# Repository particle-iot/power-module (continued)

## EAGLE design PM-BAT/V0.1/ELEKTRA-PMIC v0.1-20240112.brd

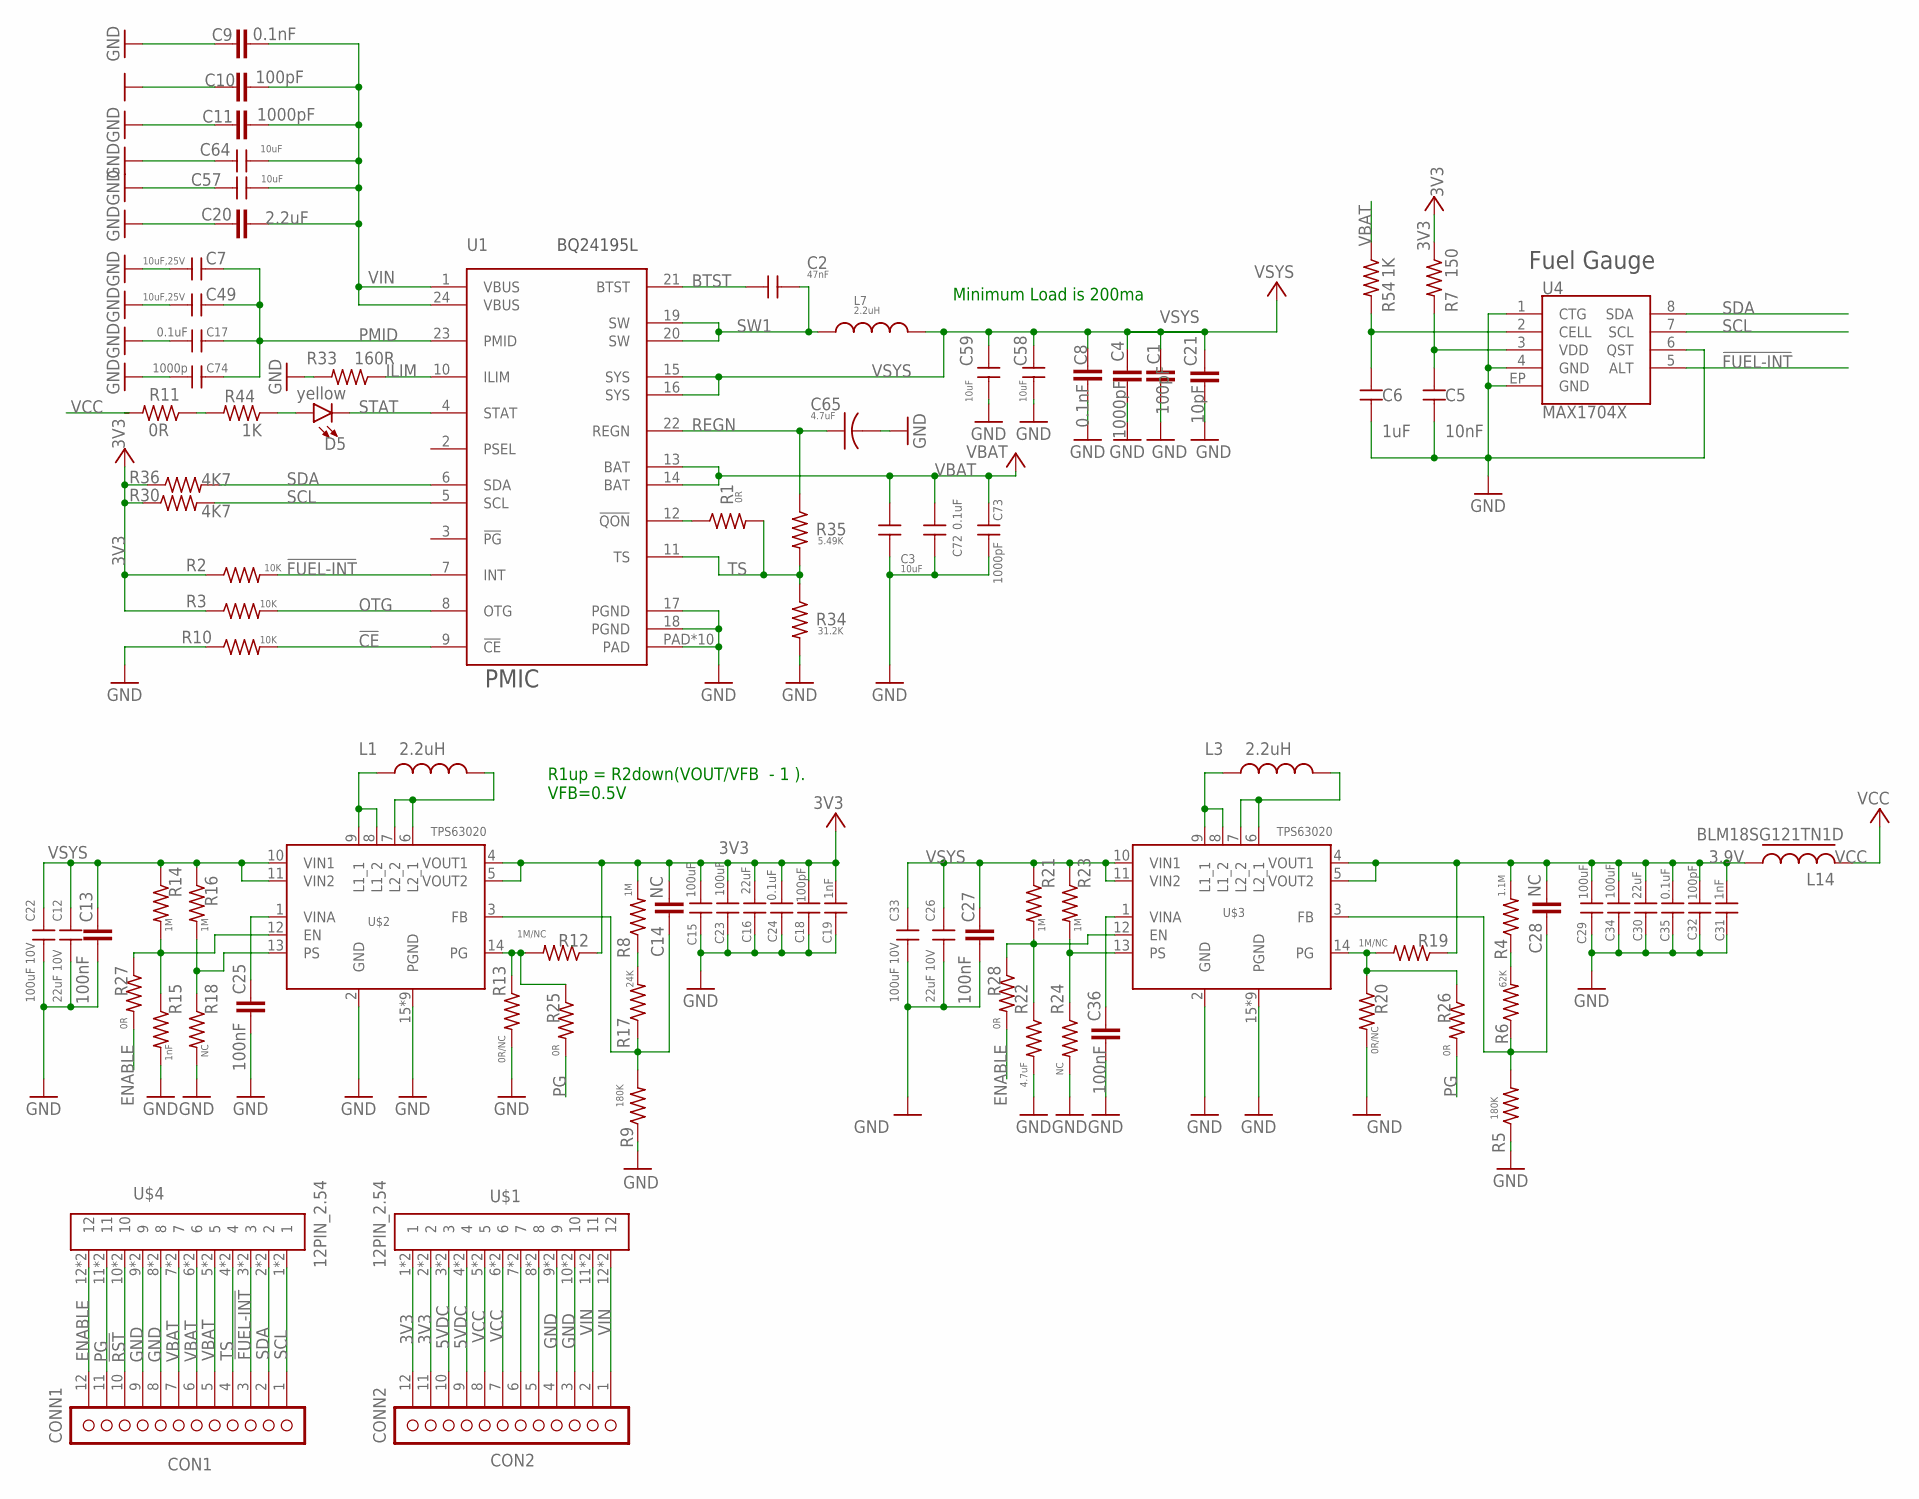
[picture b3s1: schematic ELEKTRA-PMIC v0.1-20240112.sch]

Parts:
C1, C10: 100pF; C0402_B
C2: 47nF; C-0402
C3: 10uF; C0603
C4, C11: 1000pF; C0402_B
C5: 10nF; C0402
C6: 1uF; C0402
C7, C49: 10uF,25V; C-0603A
C8, C9: 0.1nF; C0402_B
C12, C26: 22uF 10V; C0805
C13, C25, C27, C36: 100nF; C0402_B
C14, C28: NC; C0402_B
C15, C23, C29, C34: 100uF; C1206
C16, C30: 22uF; C-0603A
C17, C24, C35: 0.1uF; C0402
C18, C32: 100pF; C0402
C19, C31: 1nF; C0402
C20: 2.2uF; C0402_B
C21: 10pF; C0402_B
C22, C33: 100uF 10V; C1206
C57, C58, C59, C64: 10uF; C-0603A
C65: 4.7uF; C0603_B
C72: 0.1uF; C-0402
C73: 1000pF; C-0402
C74: 1000p; C-0402
CONN1: CON1; 1X12_SMD_STRAIGHT
CONN2: CON2; 1X12_SMD_STRAIGHT
D5: yellow; LED-0603
L1, L3: 2.2uH; INDUCTOR-VLS-E
L7: 2.2uH; INDUCTOR-4040
L14: BLM18SG121TN1D; R-0603A
R1, R11, R25, R26, R27, R28: 0R; R0402_B
R2, R3, R10: 10K; R0402_B
R4: 1.1M; R0402_B
R5, R9: 180K; R0402_B
R6: 62K; R0402_B
R7: 150; R0402_B
R8, R14, R16, R21, R23: 1M; R0402_B
R12, R19: 1M/NC; R0402_B
R13, R20: 0R/NC; R0402_B
R15: 1nF; R0402_B
R17: 24K; R0402_B
R18, R24: NC; R0402_B
R22: 4.7uF; R0402_B
R30, R36: 4K7; R0402_B
R33: 160R; R0402_B
R34: 31.2K; R0402_B
R35: 5.49K; R0402_B
R44, R54: 1K; R0402_B
U1: BQ24195L; QFN24
U4: MAX1704X; TDFN-8
U$1, U$4: 12PIN_2.54
U$2, U$3: TPS63020

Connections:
3.9V: C28.2, C29.1, C30.1, C31.1, C32.1, C34.1, C35.1, L14.2, R4.2, R19.1, U$3.4 (VOUT1), U$3.5 (VOUT2)
3V3: C14.2, C15.1, C16.1, C18.1, C19.1, C23.1, C24.1, CONN2.11, CONN2.12, R2.1, R3.1, R7.1, R8.2, R12.1, R30.1, R36.1, U$1.1, U$1.2, U$1.P$1 (1), U$1.P$2 (2), U$2.4 (VOUT1), U$2.5 (VOUT2)
5VDC: CONN2.9, CONN2.10, U$1.3, U$1.4, U$1.P$3 (3), U$1.P$4 (4)
!CE: R10.2, U1.9 (!CE)
!FUEL-INT: CONN1.3, R2.2, U1.7 (INT), U4.5 (ALT), U$4.3, U$4.P$3 (3)
!RST: CONN1.10, U$4.10, U$4.P$10 (10)
BTST: C2.1, U1.21 (BTST)
ENABLE: CONN1.12, R27.2, R28.2, U$4.12, U$4.P$12 (12)
GND: C1.1, C3.2, C4.1, C5.2, C6.2, C7.2, C8.1, C9.1, C10.1, C11.1, C12.2, C13.1, C15.2, C16.2, C17.1, C18.2, C19.2, C20.1, C21.1, C22.2, C23.2, C24.2, C25.1, C26.2, C27.1, C29.2, C30.2, C31.2, C32.2, C33.2, C34.2, C35.2, C36.1, C49.2, C57.2, C58.2, C59.2, C64.2, C65.2, C72.2, C73.2, C74.1, CONN1.8, CONN1.9, CONN2.3, CONN2.4, R5.1, R9.1, R10.1, R13.2, R15.2, R18.2, R20.2, R22.2, R24.2, R33.2, R34.2, U1.17 (PGND), U1.18 (PGND), U1.PAD, U1.PAD@1 (PAD), U1.PAD@2 (PAD), U1.PAD@3 (PAD), U1.PAD@4 (PAD), U1.PAD@5 (PAD), U1.PAD@6 (PAD), U1.PAD@7 (PAD), U1.PAD@8 (PAD), U1.PAD@9 (PAD), U4.1 (CTG), U4.4 (GND), U4.6 (QST), U4.EP (GND), U$1.9, U$1.10, U$1.P$9 (9), U$1.P$10 (10), U$2.2 (GND), U$2.15 (PGND), U$2.16 (PGND), U$2.17 (PGND), U$2.18 (PGND), U$2.19 (PGND), U$2.20 (PGND), U$2.21 (PGND), U$2.22 (PGND), U$2.23 (PGND), U$3.2 (GND), U$3.15 (PGND), U$3.16 (PGND), U$3.17 (PGND), U$3.18 (PGND), U$3.19 (PGND), U$3.20 (PGND), U$3.21 (PGND), U$3.22 (PGND), U$3.23 (PGND), U$4.8, U$4.9, U$4.P$8 (8), U$4.P$9 (9)
ILIM: R33.1, U1.10 (ILIM)
unnamed: R1.1, U1.12 (!QON)
unnamed: R11.1, R44.2
unnamed: D5.A, R44.1
unnamed: C14.1, R9.2, R17.1, U$2.3 (FB)
unnamed: C28.1, R5.2, R6.1, U$3.3 (FB)
unnamed: CONN2.6, U$1.7, U$1.P$7 (7)
unnamed: R8.1, R17.2
unnamed: R4.1, R6.2
unnamed: CONN2.5, U$1.8, U$1.P$8 (8)
unnamed: L3.P$1 (1), U$3.8 (L1_2), U$3.9 (L1_1)
unnamed: L1.P$1 (1), U$2.8 (L1_2), U$2.9 (L1_1)
unnamed: R12.2, R13.1, R25.1, U$2.14 (PG)
unnamed: R14.2, R15.1, R27.1, U$2.12 (EN)
unnamed: R16.2, R18.1, U$2.13 (PS)
unnamed: L3.P$2 (2), U$3.6 (L2_1), U$3.7 (L2_2)
unnamed: L1.P$2 (2), U$2.6 (L2_1), U$2.7 (L2_2)
unnamed: C25.2, U$2.1 (VINA)
unnamed: C36.2, U$3.1 (VINA)
unnamed: R19.2, R20.1, R26.1, U$3.14 (PG)
unnamed: R21.2, R22.1, R28.1, U$3.12 (EN)
unnamed: R23.2, R24.1, U$3.13 (PS)
unnamed: C5.1, R7.2, U4.3 (VDD)
unnamed: C6.1, R54.2, U4.2 (CELL)
OTG: R3.2, U1.8 (OTG)
PG: CONN1.11, R25.2, R26.2, U$4.11, U$4.P$11 (11)
PMID: C7.1, C17.2, C49.1, C74.2, U1.23 (PMID)
REGN: C65.1, R35.1, U1.22 (REGN)
SCL: CONN1.1, R30.2, U1.5 (SCL), U4.7 (SCL), U$4.1, U$4.P$1 (1)
SDA: CONN1.2, R36.2, U1.6 (SDA), U4.8 (SDA), U$4.2, U$4.P$2 (2)
STAT: D5.C, U1.4 (STAT)
SW1: C2.2, L7.P$1 (1), U1.19 (SW), U1.20 (SW)
TS: CONN1.4, R1.2, R34.1, R35.2, U1.11 (TS), U$4.4, U$4.P$4 (4)
VBAT: C3.1, C72.1, C73.1, CONN1.5, CONN1.6, CONN1.7, R54.1, U1.13 (BAT), U1.14 (BAT), U$4.5, U$4.6, U$4.7, U$4.P$5 (5), U$4.P$6 (6), U$4.P$7 (7)
VCC: CONN2.7, CONN2.8, L14.1, R11.2, U$1.5, U$1.6, U$1.P$5 (5), U$1.P$6 (6)
VIN: C9.2, C10.2, C11.2, C20.2, C57.1, C64.1, CONN2.1, CONN2.2, U1.1 (VBUS), U1.24 (VBUS), U$1.11, U$1.12, U$1.P$11 (11), U$1.P$12 (12)
VSYS: C1.2, C4.2, C8.2, C12.1, C13.2, C21.2, C22.1, C26.1, C27.2, C33.1, C58.1, C59.1, L7.P$2 (2), R14.1, R16.1, R21.1, R23.1, U1.15 (SYS), U1.16 (SYS), U$2.10 (VIN1), U$2.11 (VIN2), U$3.10 (VIN1), U$3.11 (VIN2)

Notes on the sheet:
Minimum Load is 200ma
PMIC
Fuel Gauge
R1up = R2down(VOUT/VFB - 1 ). VFB=0.5V

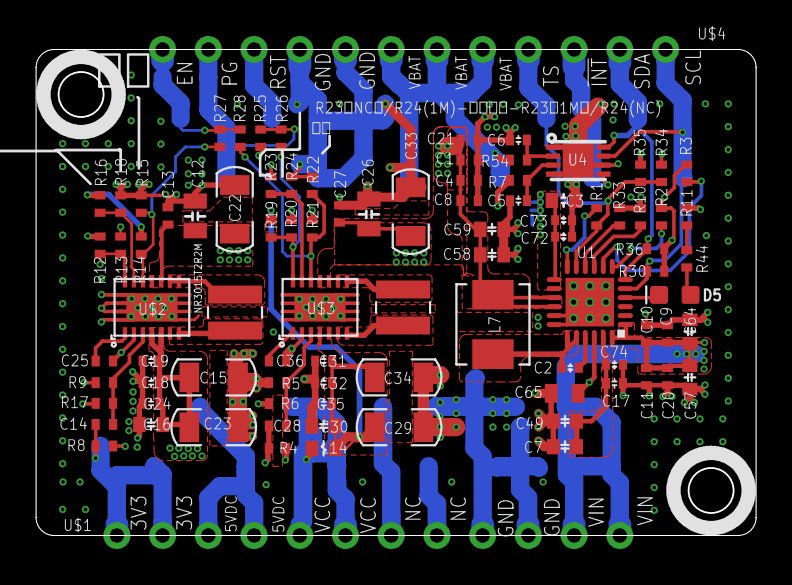
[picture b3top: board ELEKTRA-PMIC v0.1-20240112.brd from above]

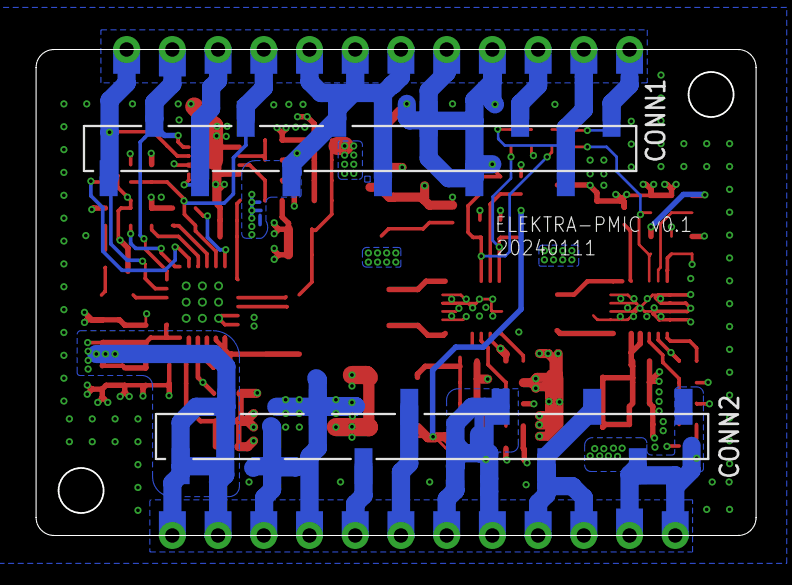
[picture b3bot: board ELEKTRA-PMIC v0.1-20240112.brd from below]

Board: 4 copper layers, 40.0 x 27.0 mm, 93 parts (2 on the bottom side), 46 nets.

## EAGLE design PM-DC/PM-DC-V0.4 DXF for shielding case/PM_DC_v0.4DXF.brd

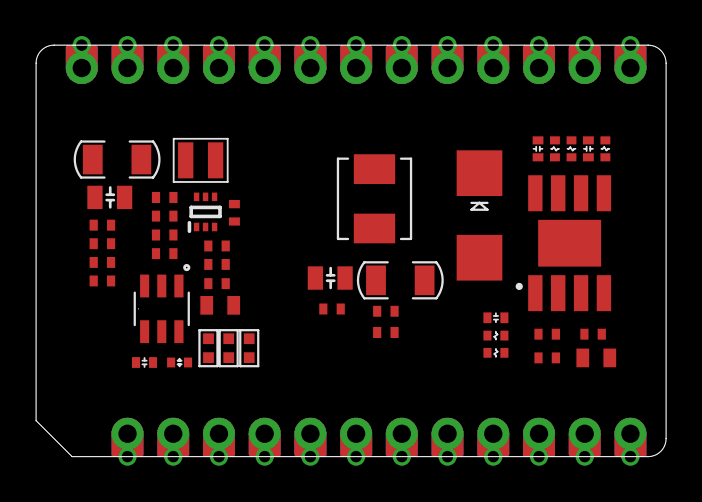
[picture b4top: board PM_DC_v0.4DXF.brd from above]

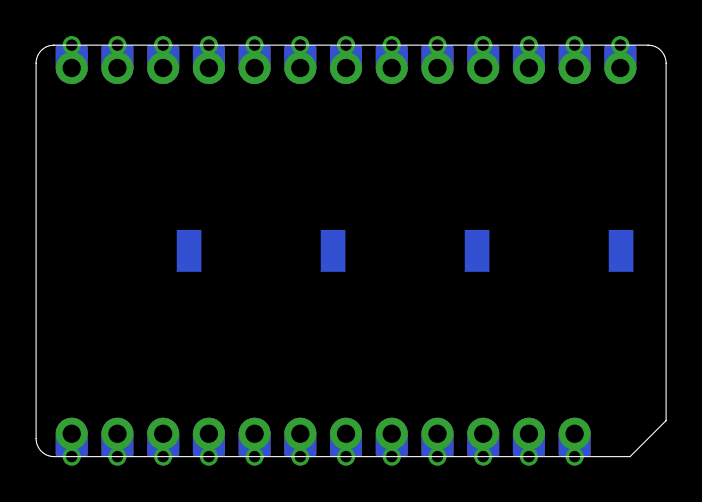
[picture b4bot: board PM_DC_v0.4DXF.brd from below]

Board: 2 copper layers, 35.0 x 22.9 mm, 49 parts (4 on the bottom side), 19 nets, no tracks yet.

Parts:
C1: 0.1uF; C0402
C2: 10uF; C0603_B
C3: 33pF; C0402_B
C4: 0.027uF; C0402
C5: 22UF; C0805
C6, C7, C9, C11: 0.1uF; C0402_B
C8: NC-33pF; C0402
C10, C12, C19: 1000pF; C0402_B
C13: 680pF; C0402_B
C14: 10uF; C0805
C15, C17: 100uF; C1206
C16: 22uF; C0603_B
C18, C20: 100pF; C0402_B
C21: 1nF; C0402_B
C22: 1000pF,25V; C0402
C23: 0.1uF; C-0402
C24, C25: 10pF; C0402_B
D2: 5A/0.55V; SMADIODE
J1: M13PTH-CST-R; 1X13-CASTELLATED
J2: M12PTH-CST-R; 1X12-CASTELLATED
L1: 1.5uH; INDUCTOR-2520
L4: 2.2uH; INDUCTOR-4040
R1: 44.2K; R0402_B
R2, R8: 12K; R-0402S
R3: 76.8K; R-0402S
R4: 100K; R-0402S
R5: 44.2K; R-0402S
R6: 100K; R0402
R7: 10K; R0402
R9: 0R; R0402_B
R11: 10K; R0402_B
R12: 10K/NC; R0402
R58: 200K; R0402_B
U2: LMR14030; SO_POWERPAD_8
U3: MP1601GTF-Z; SOTFL50P160X60-6N
U5: TPS22918; SOT-23-6
U$1, U$2, U$4, U$5: TP; TP_2.33X1.37

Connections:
3V3_AUX: C23.1, J2.2, J2.@2, R7.1, R12.1, U5.6
+3V3: C3.2, C7.2, C13.1, C14.1, C15.1, C18.2, C21.2, J2.1, J2.@1, L1.2, R58.1, U3.6, U5.1
ENABLE: J1.13, J1.@13, R8.1, U2.3
EN_AUX: J2.7, J2.@7, R6.1, U5.3
FB: C13.2, R1.1, R9.2, U3.1
GND: C2.2, C3.1, C4.2, C5.2, C6.1, C7.1, C9.1, C10.1, C11.1, C12.1, C14.2, C15.2, C16.2, C17.2, C18.1, C19.1, C20.1, C21.1, C22.2, C23.2, C24.1, C25.1, D2.A, J1.9, J1.10, J1.@9, J1.@10, J2.9, J2.10, J2.@9, J2.@10, R1.2, R2.1, R5.1, R6.2, R12.2, U2.7, U2.EP, U3.2, U5.2, U$1.1, U$2.1, U$4.1, U$5.1
unnamed: R7.2, U5.5
unnamed: C8.1, R4.1, R5.2, U2.5
unnamed: R11.2, U3.5
unnamed: R9.1, R58.2
unnamed: C4.1, U2.6
unnamed: C1.2, D2.C, L4.P$1, U2.8
unnamed: C1.1, U2.1
unnamed: R2.2, U2.4
unnamed: R3.1, R4.2
unnamed: C22.1, U5.4
SW: L1.1, U3.4
VCC: C2.1, C5.1, C6.2, C8.2, C11.2, C12.2, C17.1, C19.2, C20.2, C25.2, J2.5, J2.6, J2.@5, J2.@6, L4.P$2, R3.2, R11.1, U3.3
VIN: C9.2, C10.2, C16.1, C24.2, J2.11, J2.12, J2.@11, J2.@12, R8.2, U2.2

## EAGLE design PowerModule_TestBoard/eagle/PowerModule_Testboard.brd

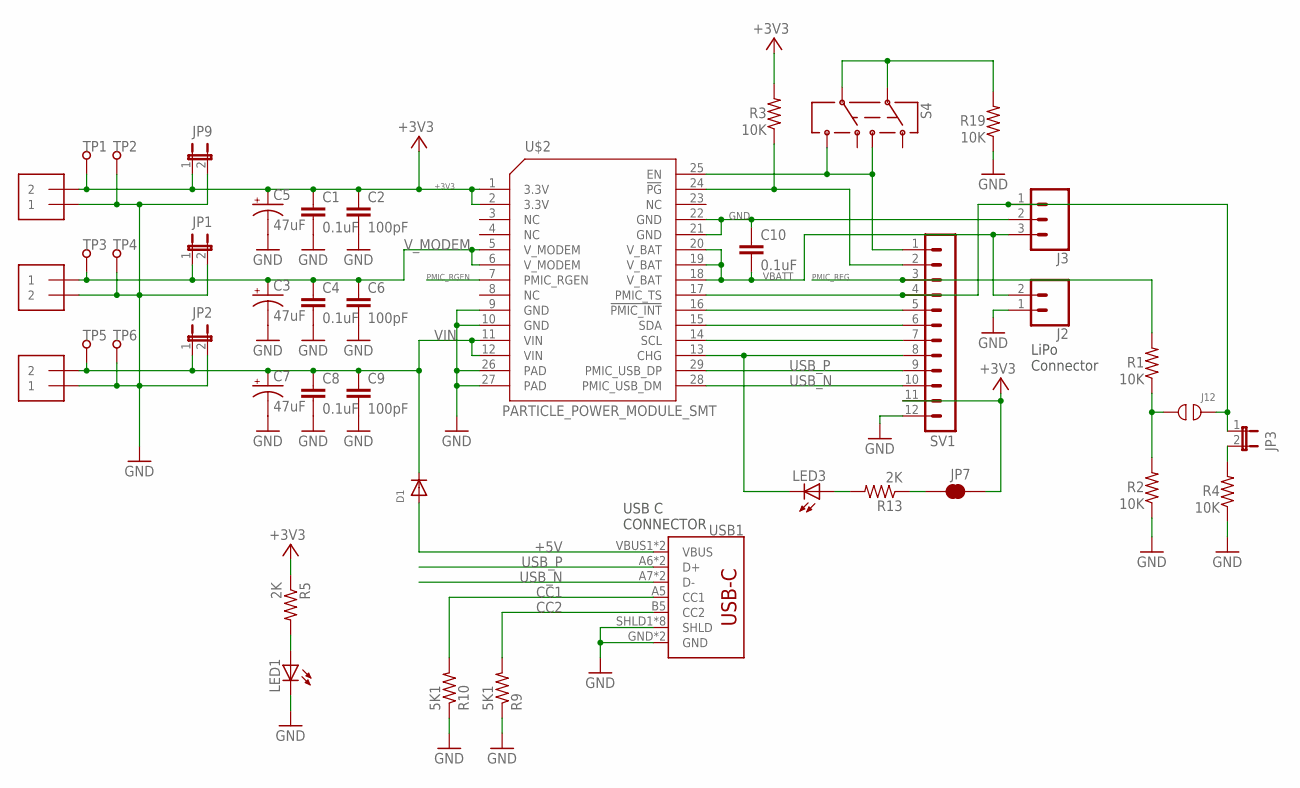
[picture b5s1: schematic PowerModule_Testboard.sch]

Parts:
C1, C4, C8, C10: 0.1uF; 0603
C2, C6, C9: 100pF; 0603
C3, C5, C7: 47uF; NIC_10X10.5_CAP
D1: DIODE_SOD-123FL; SOD-123FL
J1, J4, J5: 1X2-3.5MM
J2: CONN_02-JST-2MM-SMT; JST-2-SMD@2
J3: CONN_03JST-SMD-VERT; JST-3-SMD-VERT
J12: TP_OPEN
JP1, JP2, JP3, JP9: JUMPER2
JP7: JUMPER-SMT_2_NC_TRACE_NO-SILK; SMT-JUMPER_2_NC_TRACE_NO-SILK
LED1, LED3: LEDCHIP-LED0603; CHIP-LED0603
R1, R2, R3, R4, R19: 10K; R0603_P
R5, R13: 2K; R0603_P
R9, R10: 5K1; R0603_P
S4: SWITCH-DPDT; SWITCH-2.5X3.2-6
SV1: MA12-1
TP1, TP2, TP3, TP4, TP5, TP6: TP-S2751-46R; S2751-46R
U$2: PARTICLE_POWER_MODULE_SMT
USB1: USB_C16PIN; USB-C-16P

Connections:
+3V3: C1.1, C2.1, C5.+, J4.2, JP7.1, JP9.1, R3.2, R5.1, SV1.11, TP1.1, U$2.1 (3.3V), U$2.2 (3.3V)
+5V: D1.A, USB1.VBUS1 (VBUS), USB1.VBUS2 (VBUS)
CC1: R10.2, USB1.A5 (CC1)
CC2: R9.2, USB1.B5 (CC2)
GND: C1.2, C2.2, C3.-, C4.2, C5.-, C6.2, C7.-, C8.2, C9.2, C10.1, J1.2, J2.1 (2), J3.2, J4.1, J5.1, JP1.2, JP2.2, JP9.2, LED1.C, R2.1, R4.1, R9.1, R10.1, R19.1, SV1.12, TP2.1, TP4.1, TP6.1, U$2.9 (GND), U$2.10 (GND), U$2.21 (GND), U$2.22 (GND), U$2.26 (PAD), U$2.27 (PAD), USB1.GND, USB1.GND2 (GND), USB1.SHLD1 (SHLD), USB1.SHLD2 (SHLD), USB1.SHLD3 (SHLD), USB1.SHLD4 (SHLD), USB1.SHLD5 (SHLD), USB1.SHLD6 (SHLD), USB1.SHLD7 (SHLD), USB1.SHLD8 (SHLD)
unnamed: JP7.2, R13.1
unnamed: R19.2, S4.2, S4.5
unnamed: J12.1, R1.1, R2.2
unnamed: R3.1, SV1.2, U$2.24 (!PG)
unnamed: J3.1, J12.2, JP3.1, SV1.4, U$2.17 (PMIC_TS)
unnamed: SV1.5, U$2.16 (!PMIC_INT)
unnamed: SV1.6, U$2.15 (SDA)
unnamed: SV1.7, U$2.14 (SCL)
unnamed: JP3.2, R4.2
unnamed: LED3.C, SV1.8, U$2.13 (CHG)
unnamed: LED3.A, R13.2
unnamed: S4.3, S4.6, SV1.1, U$2.25 (EN)
unnamed: LED1.A, R5.2
PMIC_REG: R1.2, SV1.3
PMIC_RGEN: U$2.7 (PMIC_RGEN)
USB_N: SV1.10, U$2.28 (PMIC_USB_DM), USB1.A7 (D-), USB1.B7 (D-)
USB_P: SV1.9, U$2.29 (PMIC_USB_DP), USB1.A6 (D+), USB1.B6 (D+)
VBATT: C10.2, J2.2 (1), J3.3, U$2.18 (V_BAT), U$2.19 (V_BAT), U$2.20 (V_BAT)
VIN: C7.+, C8.1, C9.1, D1.C, J5.2, JP2.1, TP5.1, U$2.11 (VIN), U$2.12 (VIN)
V_MODEM: C3.+, C4.1, C6.1, J1.1, JP1.1, TP3.1, U$2.5 (V_MODEM), U$2.6 (V_MODEM)

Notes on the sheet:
USB C CONNECTOR
LiPo Connector

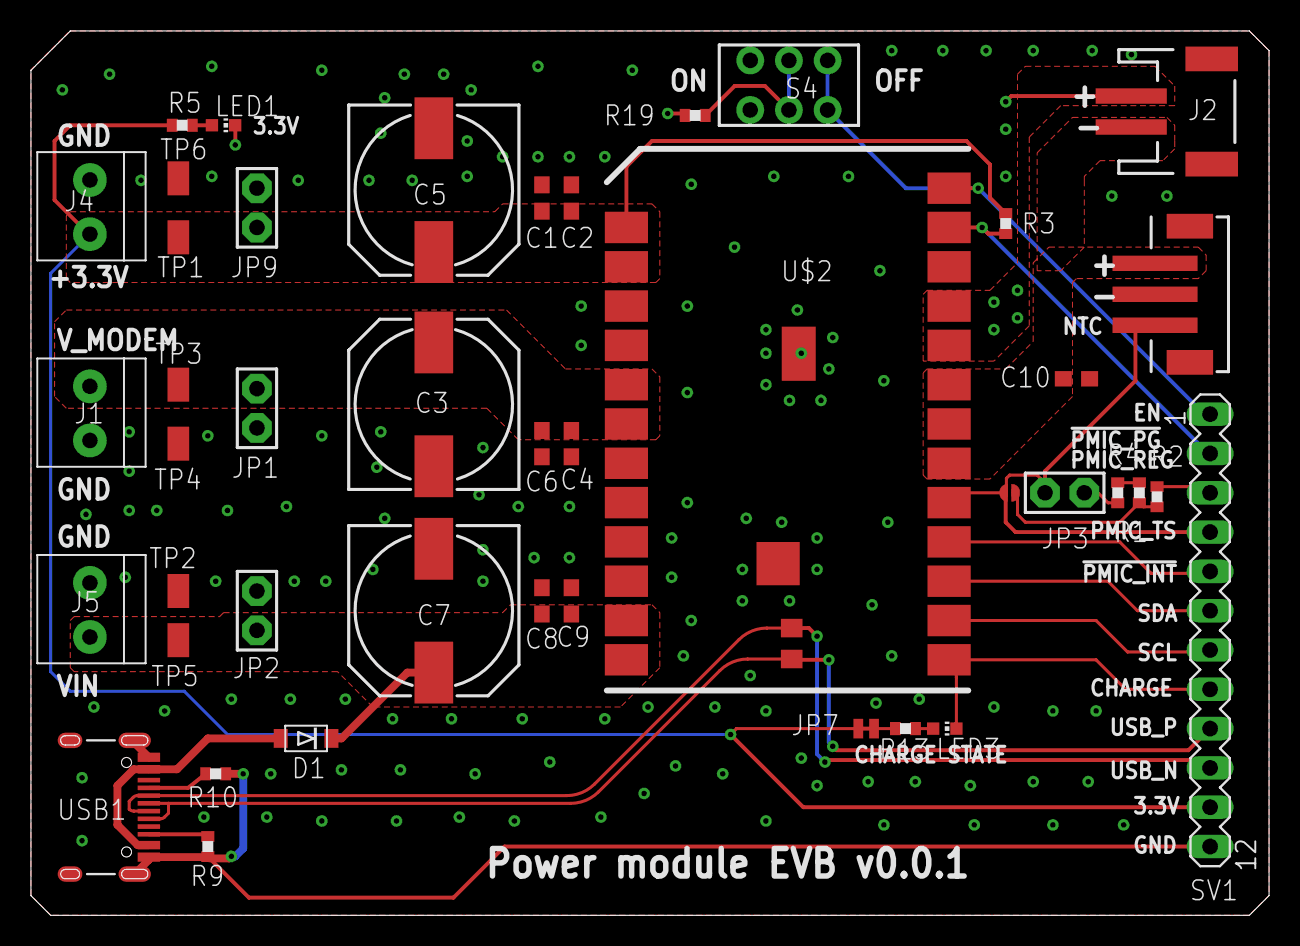
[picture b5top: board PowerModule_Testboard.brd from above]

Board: 2 copper layers, 80.0 x 57.1 mm, 43 parts (0 on the bottom side), 24 nets.
